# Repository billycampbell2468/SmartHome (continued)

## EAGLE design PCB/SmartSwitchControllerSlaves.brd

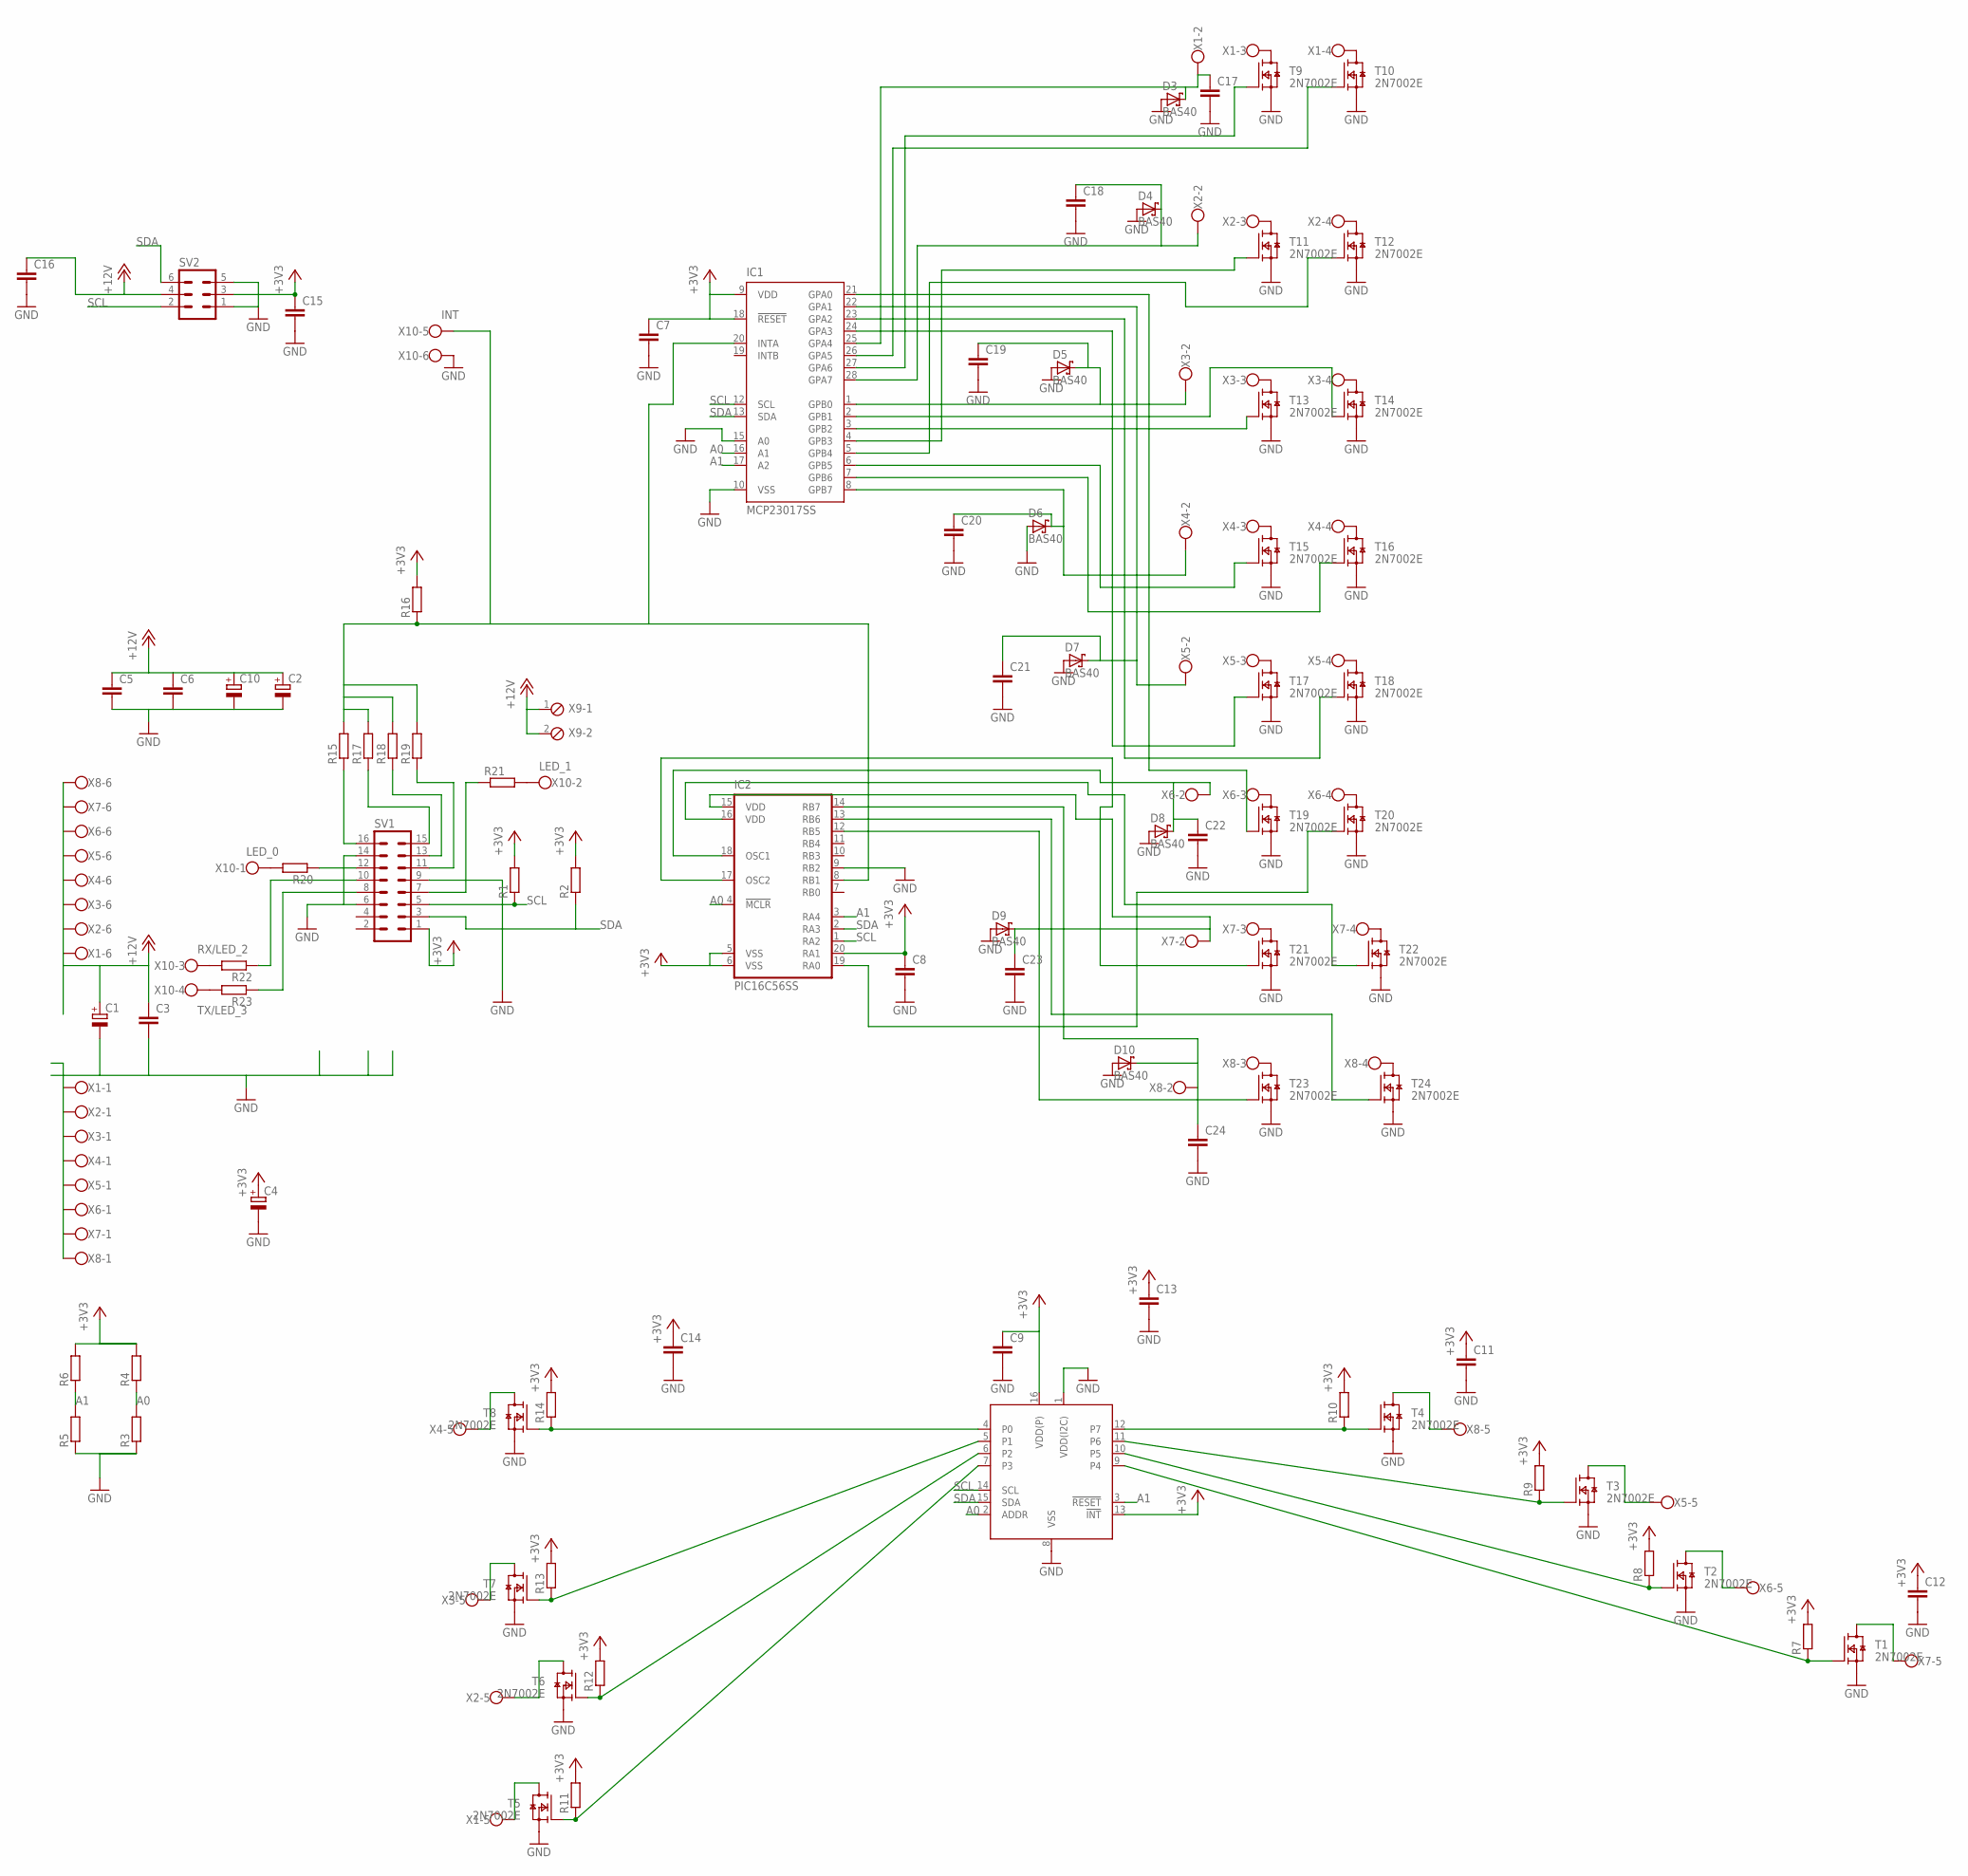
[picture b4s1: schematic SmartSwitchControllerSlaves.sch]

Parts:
C1, C2, C4, C10: CPOL-EUUD-6,3X7,7; UD-6,3X7,7_NICHICON
C3, C5, C7, C8, C9, C11, C12: C-EUC0603; C0603
C6, C13, C14, C15, C16, C17, C18, C19, C20, C21, C22, C23, C24: C-EUC0805; C0805
D3, D4, D5, D6, D7, D8, D9, D10: BAS40; SOT23
IC1: MCP23017SS; SSOP28
IC2: PIC16C56SS; SSOP20
R1, R2, R15, R16, R17, R18, R19, R20, R21, R22, R23: R-EU_R0603; R0603
R3, R4, R5, R6, R7, R8, R9, R10, R11, R12, R13, R14: R-EU_R0402; R0402
SV1: MA08-2
SV2: MA03-2
T1, T2, T3, T4, T5, T6, T7, T8, T9, T10, T11, T12, T13, T14, T15, T16, T17, T18, T19, T20, T21, T22, T23, T24: 2N7002E; SOT23
U1: PCAL6408APW; SOT403-1
X1, X2, X3, X4, X5, X6, X7, X8, X10: W237-6
X9: MPT2; 2POL254

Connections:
+3V3: C4.+, C7.1, C8.1, C9.1, C11.1, C12.1, C13.1, C14.1, C15.1, IC1.9 (VDD), IC1.18 (!RESET), IC2.5 (VSS), IC2.6 (VSS), IC2.20 (RA1), R1.2, R2.2, R4.2, R6.2, R7.2, R8.2, R9.2, R10.2, R11.2, R12.2, R13.2, R14.2, R16.2, SV1.1, SV2.3, U1.13 (!INT!), U1.16 (VDD(P))
+12V: C1.+, C2.+, C3.1, C5.1, C6.1, C10.+, C16.1, SV2.4, X1.6, X2.6, X3.6, X4.6, X5.6, X6.6, X7.6, X8.6, X9.1, X9.2
A0: IC1.16 (A1), IC2.4 (!MCLR), R3.2, R4.1, U1.2 (ADDR)
A1: IC1.17 (A2), IC2.3 (RA4), R5.2, R6.1, U1.3 (!RESET!)
GND: C1.-, C2.-, C3.2, C4.-, C5.2, C6.2, C7.2, C8.2, C9.2, C10.-, C11.2, C12.2, C13.2, C14.2, C15.2, C16.2, C17.2, C18.2, C19.2, C20.2, C21.2, C22.2, C23.2, C24.2, D3.1 (A), D4.1 (A), D5.1 (A), D6.1 (A), D7.1 (A), D8.1 (A), D9.1 (A), D10.1 (A), IC1.10 (VSS), IC1.15 (A0), IC2.9 (RB2), R3.1, R5.1, SV1.6, SV1.9, SV1.14, SV2.1, SV2.5, T1.2 (S), T2.2 (S), T3.2 (S), T4.2 (S), T5.2 (S), T6.2 (S), T7.2 (S), T8.2 (S), T9.2 (S), T10.2 (S), T11.2 (S), T12.2 (S), T13.2 (S), T14.2 (S), T15.2 (S), T16.2 (S), T17.2 (S), T18.2 (S), T19.2 (S), T20.2 (S), T21.2 (S), T22.2 (S), T23.2 (S), T24.2 (S), U1.1 (VDD(I2C)), U1.8 (VSS), X1.1, X2.1, X3.1, X4.1, X5.1, X6.1, X7.1, X8.1, X10.6
unnamed: T9.3 (D), X1.3
unnamed: T10.3 (D), X1.4
unnamed: R20.2, X10.1
unnamed: R21.2, X10.2
unnamed: T11.3 (D), X2.3
unnamed: T12.3 (D), X2.4
unnamed: T13.3 (D), X3.3
unnamed: T14.3 (D), X3.4
unnamed: R22.2, X10.3
unnamed: T16.3 (D), X4.4
unnamed: T15.3 (D), X4.3
unnamed: T17.3 (D), X5.3
unnamed: T18.3 (D), X5.4
unnamed: T20.3 (D), X6.4
unnamed: T19.3 (D), X6.3
unnamed: T21.3 (D), X7.3
unnamed: T22.3 (D), X7.4
unnamed: T23.3 (D), X8.3
unnamed: IC1.21 (GPA0), T19.1 (G)
unnamed: C21.1, D7.3 (C), IC1.22 (GPA1), X5.2
unnamed: IC1.23 (GPA2), T18.1 (G)
unnamed: IC1.24 (GPA3), T17.1 (G)
unnamed: C17.1, D3.3 (C), IC1.25 (GPA4), X1.2
unnamed: IC1.26 (GPA5), T10.1 (G)
unnamed: IC1.27 (GPA6), T9.1 (G)
unnamed: C18.1, D4.3 (C), IC1.28 (GPA7), X2.2
unnamed: IC1.5 (GPB4), T12.1 (G)
unnamed: IC1.4 (GPB3), T11.1 (G)
unnamed: C19.1, D5.3 (C), IC1.1 (GPB0), X3.2
unnamed: IC1.2 (GPB1), T14.1 (G)
unnamed: IC1.3 (GPB2), T13.1 (G)
unnamed: IC1.6 (GPB5), T15.1 (G)
unnamed: IC1.7 (GPB6), T16.1 (G)
unnamed: C20.1, D6.3 (C), IC1.8 (GPB7), X4.2
unnamed: C23.1, D9.3 (C), IC2.15 (VDD), X7.2
unnamed: IC2.16 (VDD), T22.1 (G)
unnamed: IC2.17 (OSC2), T21.1 (G)
unnamed: C22.1, D8.3 (C), IC2.18 (OSC1), X6.2
unnamed: IC2.19 (RA0), T20.1 (G)
unnamed: C24.1, D10.3 (C), IC2.14 (RB7), X8.2
unnamed: IC2.13 (RB6), T24.1 (G)
unnamed: IC2.12 (RB5), T23.1 (G)
unnamed: R11.1, T5.1 (G), U1.7 (P3)
unnamed: R12.1, T6.1 (G), U1.6 (P2)
unnamed: R13.1, T7.1 (G), U1.5 (P1)
unnamed: R14.1, T8.1 (G), U1.4 (P0)
unnamed: R7.1, T1.1 (G), U1.9 (P4)
unnamed: R8.1, T2.1 (G), U1.10 (P5)
unnamed: R9.1, T3.1 (G), U1.11 (P6)
unnamed: R10.1, T4.1 (G), U1.12 (P7)
unnamed: IC1.20 (INTA), IC2.8 (RB1), R15.2, R16.1, R17.2, R18.2, R19.2, X10.5
unnamed: R23.2, X10.4
unnamed: T1.3 (D), X7.5
unnamed: T2.3 (D), X6.5
unnamed: T3.3 (D), X5.5
unnamed: T4.3 (D), X8.5
unnamed: T5.3 (D), X1.5
unnamed: T6.3 (D), X2.5
unnamed: T24.3 (D), X8.4
unnamed: T7.3 (D), X3.5
unnamed: T8.3 (D), X4.5
unnamed: R15.1, SV1.16
unnamed: R17.1, SV1.15
unnamed: R18.1, SV1.13
unnamed: R19.1, SV1.11
unnamed: R20.1, SV1.12
unnamed: R21.1, SV1.7
unnamed: R22.1, SV1.10
unnamed: R23.1, SV1.8
SCL: IC1.12 (SCL), IC2.1 (RA2), R1.1, SV1.5, SV2.2, U1.14 (SCL)
SDA: IC1.13 (SDA), IC2.2 (RA3), R2.1, SV1.3, SV2.6, U1.15 (SDA)

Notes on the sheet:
RX/LED_2
TX/LED_3
LED_0
LED_1
INT

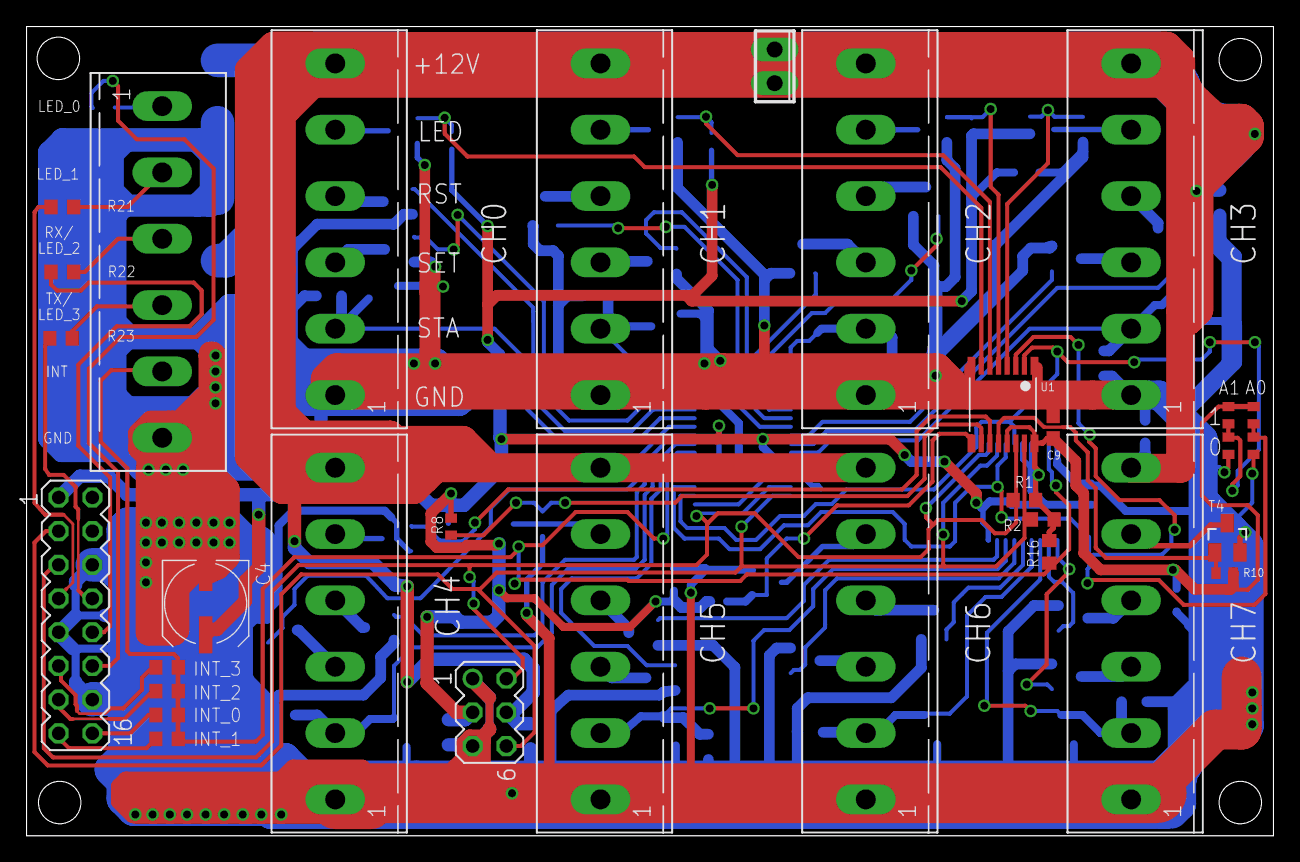
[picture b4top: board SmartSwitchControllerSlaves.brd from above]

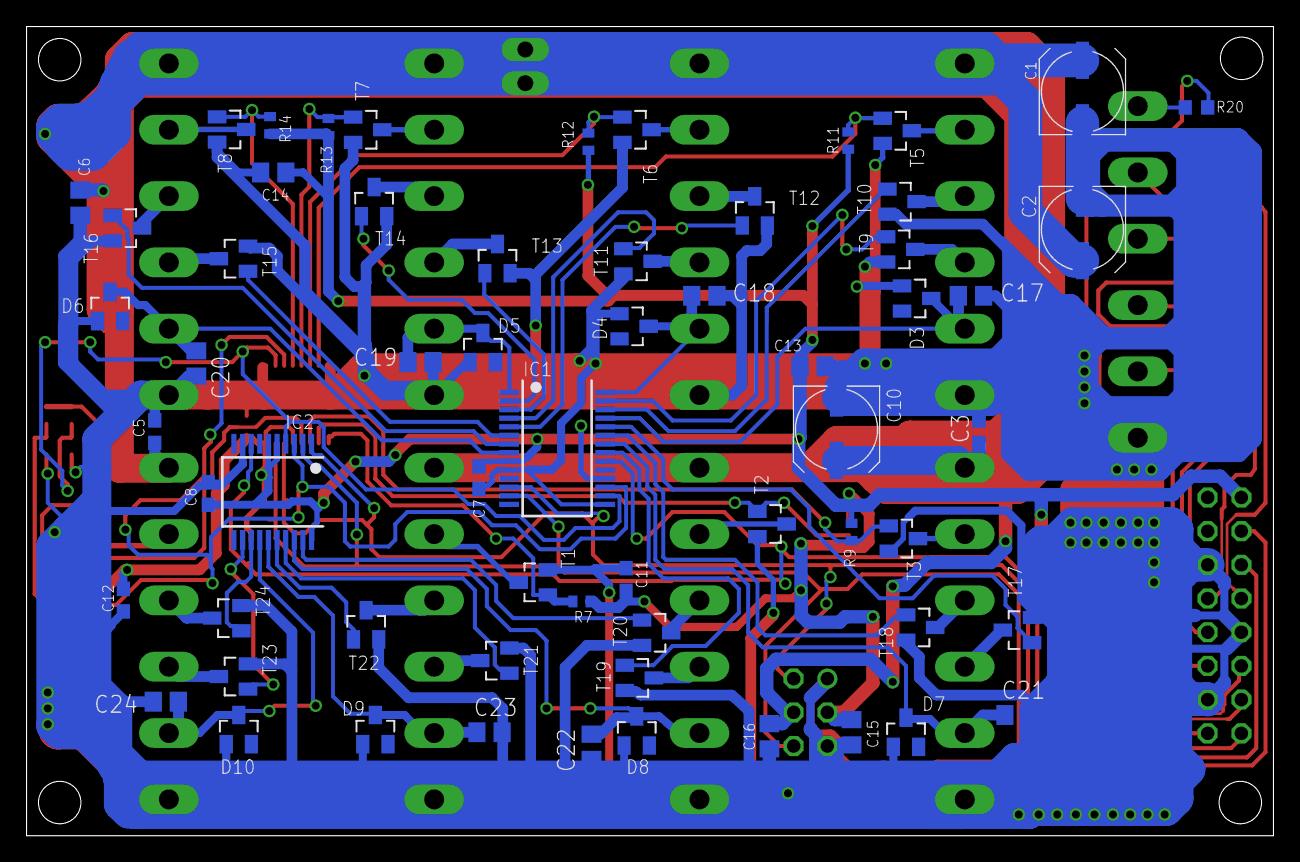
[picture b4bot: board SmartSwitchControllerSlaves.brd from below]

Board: 2 copper layers, 94.0 x 61.0 mm, 94 parts (62 on the bottom side), 76 nets.

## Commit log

2022-02-19 Create test
